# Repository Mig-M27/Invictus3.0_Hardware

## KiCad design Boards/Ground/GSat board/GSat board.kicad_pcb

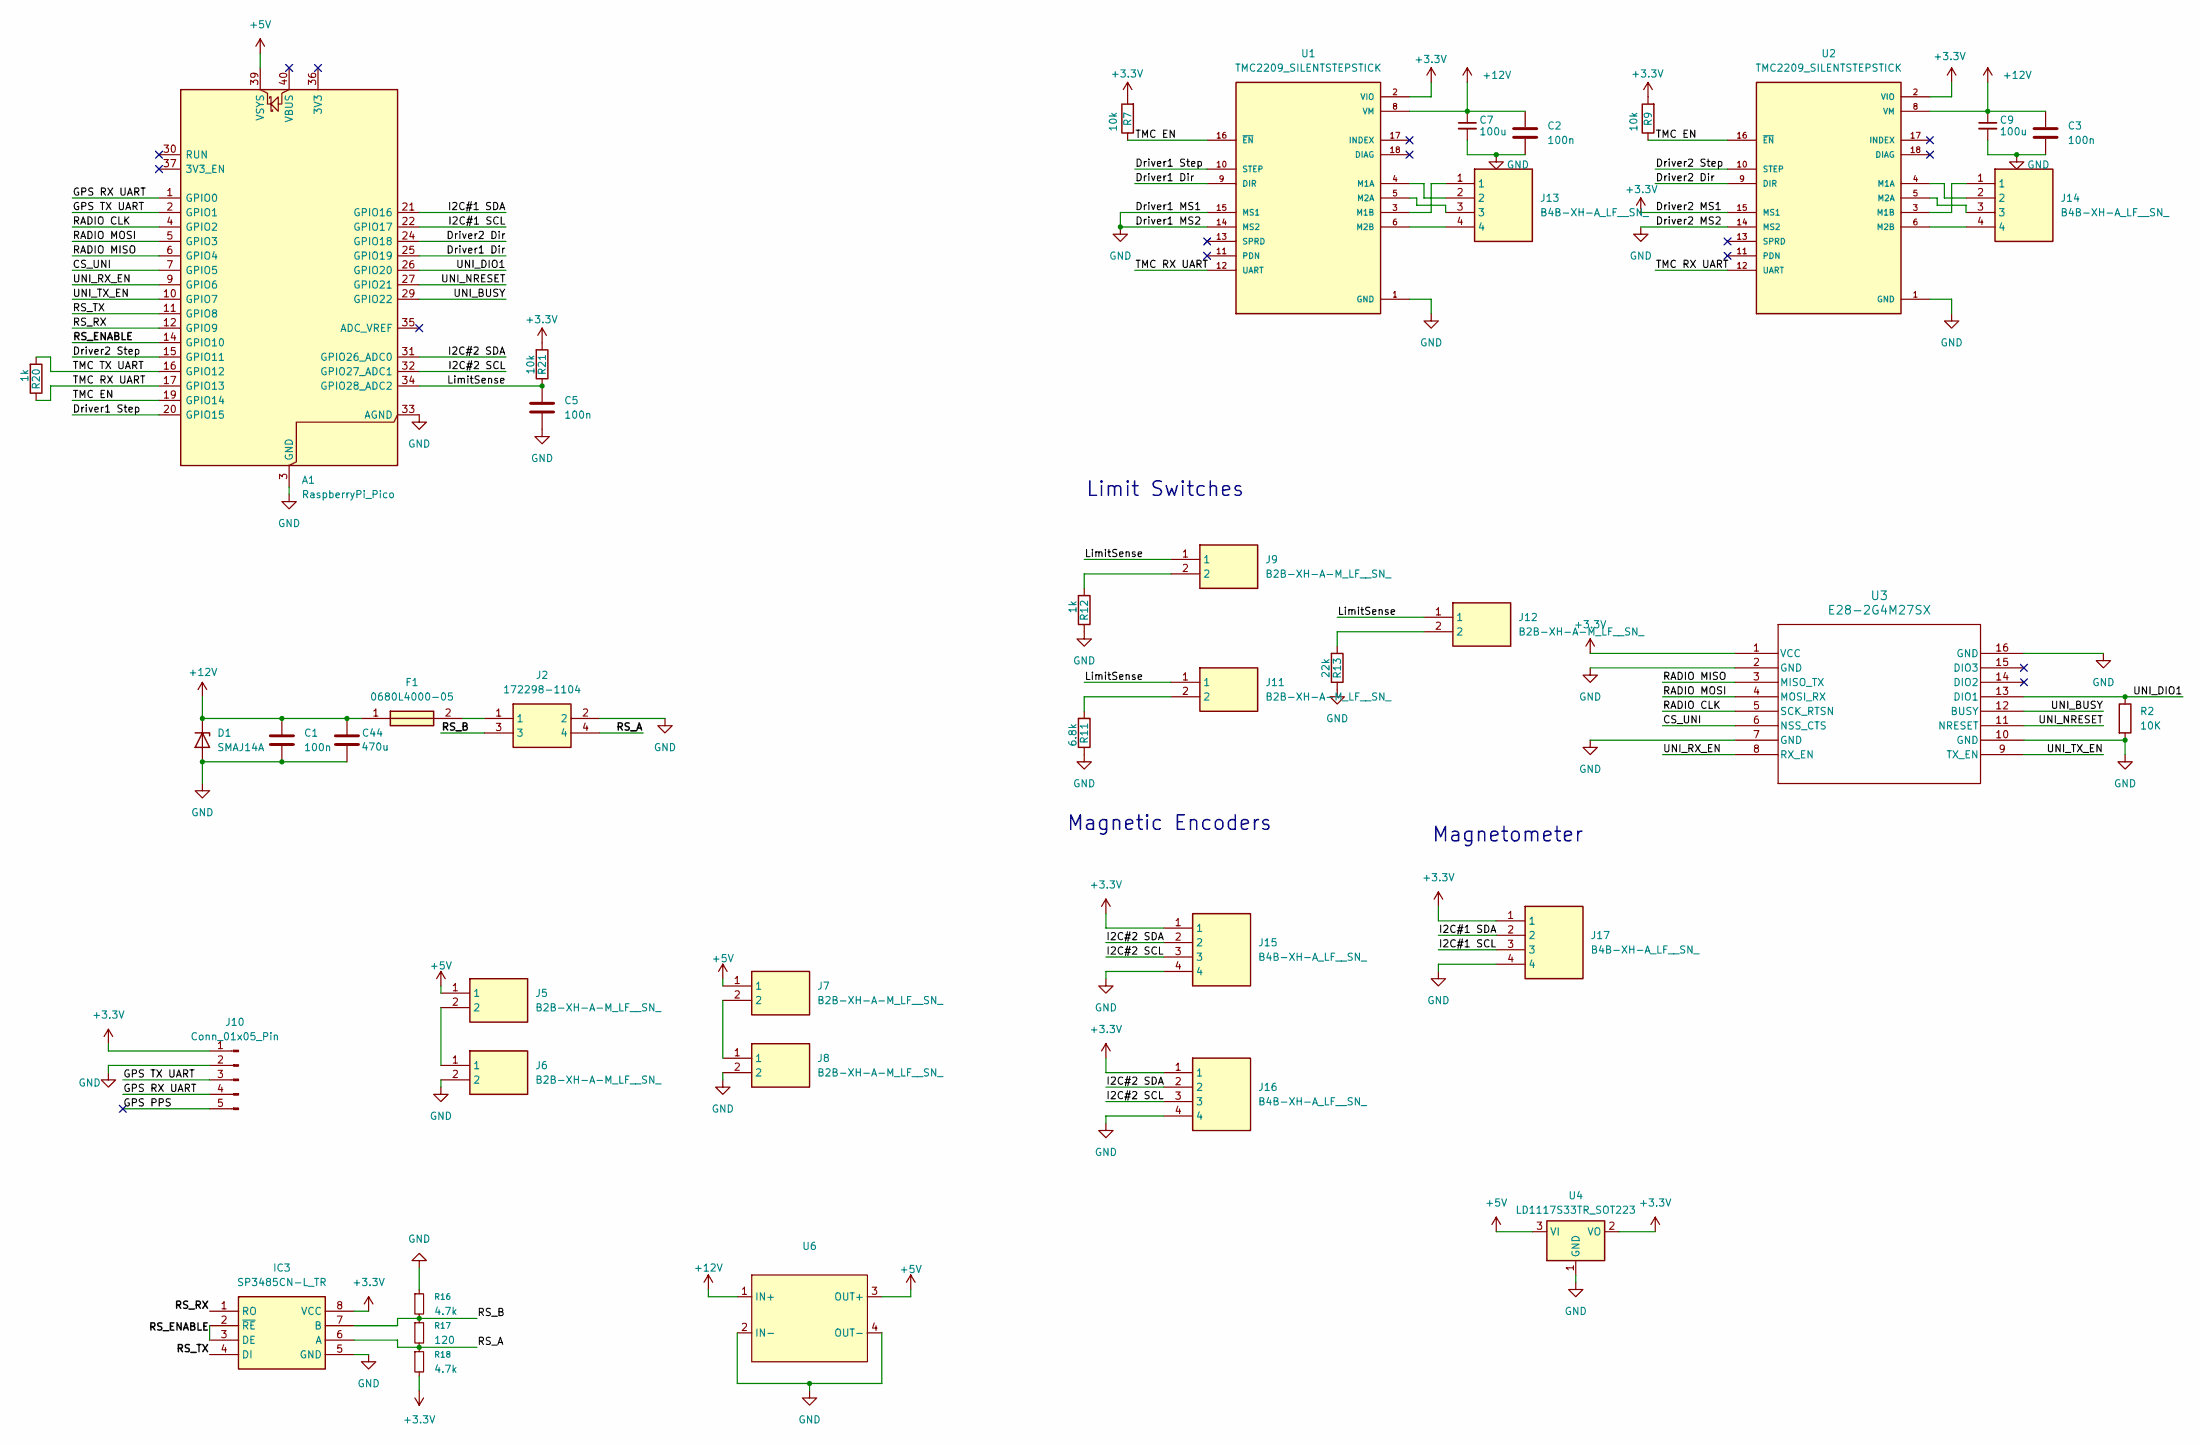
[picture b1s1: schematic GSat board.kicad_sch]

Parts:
A1: RaspberryPi_Pico; RaspberryPi_Pico_Common_Unspecified
C1, C2, C3, C5: 100n; C_0805_2012Metric_Pad1.18x1.45mm_HandSolder
C7, C9: 100u; CP_Elec_6.3x7.7
C44: 470u; CP_Elec_10x10
D1: SMAJ14A; D_SMB
F1: 0680L4000-05; Fuse_2512_6332Metric; Mouser Part Number 530-0ABB-6000-TM
IC3: SP3485CN-L_TR; SOIC127P600X175-8N; Mouser Part Number 701-SP3485CN-L/TR
J2: 172298-1104; 172298-YY04; Mouser Part Number 538-172298-1104
J5, J6, J7, J8, J9, J11, J12: B2B-XH-A-M_LF__SN_; B2BXHAMLFSN; Mouser Part Number 306-B2B-XH-A-MLFS
J10: Conn_01x05_Pin; PinSocket_1x05_P2.54mm_Vertical
J13, J14, J15, J16, J17: B4B-XH-A_LF__SN_; B4BXHALFSN; Mouser Part Number 306-B4BXHALFSN
R2: 10K; R_0805_2012Metric_Pad1.20x1.40mm_HandSolder
R7, R9, R21: 10k; R_0805_2012Metric_Pad1.20x1.40mm_HandSolder
R11: 6.8k; R_0805_2012Metric_Pad1.20x1.40mm_HandSolder
R12, R20: 1k; R_0805_2012Metric_Pad1.20x1.40mm_HandSolder
R13: 22k; R_0805_2012Metric_Pad1.20x1.40mm_HandSolder
R16: 4.7k; R_0603_1608Metric_Pad0.98x0.95mm_HandSolder
R17: 120; R_0603_1608Metric_Pad0.98x0.95mm_HandSolder
R18: 4.7k; R_0805_2012Metric_Pad1.20x1.40mm_HandSolder
U1, U2: TMC2209_SILENTSTEPSTICK; MODULE_TMC2209_SILENTSTEPSTICK; PARTREV 1.20
U3: E28-2G4M27SX; Radio_Module_PST
U4: LD1117S33TR_SOT223; SOT-223-3_TabPin2
U6: DCDC_Module

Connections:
+3.3V: IC3.8 (VCC), J10.1, J15.1, J16.1, J17.1, R7.2, R9.2, R18.2, R21.2, U1.2 (VIO), U2.2 (VIO), U2.15 (MS1), U3.1 (VCC), U4.2 (VO)
+5V: A1.39 (VSYS), J5.1, J7.1, U4.3 (VI), U6.3 (OUT+)
+12V: C1.1, C2.1, C3.1, C7.1, C9.1, C44.1, D1.1 (K), F1.1, U1.8 (VM), U2.8 (VM), U6.1 (IN+)
/CS_UNI: A1.7 (GPIO5), U3.6 (NSS_CTS)
/Driver1 Dir: A1.25 (GPIO19), U1.9 (DIR)
/Driver1 Step: A1.20 (GPIO15), U1.10 (STEP)
/Driver2 Dir: A1.24 (GPIO18), U2.9 (DIR)
/Driver2 Step: A1.15 (GPIO11), U2.10 (STEP)
/GPS PPS: J10.5
/GPS RX UART: A1.1 (GPIO0), J10.4
/GPS TX UART: A1.2 (GPIO1), J10.3
/I2C#1 SCL: A1.22 (GPIO17), J17.3
/I2C#1 SDA: A1.21 (GPIO16), J17.2
/I2C#2 SCL: A1.32 (GPIO27_ADC1), J15.3, J16.3
/I2C#2 SDA: A1.31 (GPIO26_ADC0), J15.2, J16.2
/LimitSense: A1.34 (GPIO28_ADC2), C5.1, J9.1, J11.1, J12.1, R21.1
/RADIO CLK: A1.4 (GPIO2), U3.5 (SCK_RTSN)
/RADIO MISO: A1.6 (GPIO4), U3.3 (MISO_TX)
/RADIO MOSI: A1.5 (GPIO3), U3.4 (MOSI_RX)
/RS_A: IC3.6 (A), J2.4, R17.2, R18.1
/RS_B: IC3.7 (B), J2.3, R16.2, R17.1
/RS_ENABLE: A1.14 (GPIO10), IC3.2 (~RE), IC3.3 (DE)
/RS_RX: A1.12 (GPIO9), IC3.1 (RO)
/RS_TX: A1.11 (GPIO8), IC3.4 (DI)
/TMC EN: A1.19 (GPIO14), R7.1, R9.1, U1.16 (~EN), U2.16 (~EN)
/TMC RX UART: A1.17 (GPIO13), R20.1, U1.12 (UART), U2.12 (UART)
/TMC TX UART: A1.16 (GPIO12), R20.2
/UNI_BUSY: A1.29 (GPIO22), U3.12 (BUSY)
/UNI_DIO1: A1.26 (GPIO20), R2.1, U3.13 (DIO1)
/UNI_NRESET: A1.27 (GPIO21), U3.11 (NRESET)
/UNI_RX_EN: A1.9 (GPIO6), U3.8 (RX_EN)
/UNI_TX_EN: A1.10 (GPIO7), U3.9 (TX_EN)
GND: A1.3 (GND), A1.8 (GND), A1.13 (GND), A1.18 (GND), A1.23 (GND), A1.28 (GND), A1.33 (AGND), A1.38 (GND), C1.2, C2.2, C3.2, C5.2, C7.2, C9.2, C44.2, D1.2 (A), IC3.5 (GND), J2.2, J6.2, J8.2, J10.2, J15.4, J16.4, J17.4, R2.2, R11.1, R12.1, R13.1, R16.1, U1.1 (GND), U1.7 (GND), U1.14 (MS2), U1.15 (MS1), U2.1 (GND), U2.7 (GND), U2.14 (MS2), U3.2 (GND), U3.7 (GND), U3.10 (GND), U3.16 (GND), U4.1 (GND), U6.2 (IN-), U6.4 (OUT-)
unnamed: F1.2, J2.1
unnamed: J5.2, J6.1
unnamed: J7.2, J8.1
unnamed: J9.2, R12.2
unnamed: J11.2, R11.2
unnamed: J12.2, R13.2
unnamed: J13.2, U1.4 (M1A)
unnamed: J13.1, U1.3 (M1B)
unnamed: J13.3, U1.5 (M2A)
unnamed: J13.4, U1.6 (M2B)
unnamed: J14.2, U2.4 (M1A)
unnamed: J14.1, U2.3 (M1B)
unnamed: J14.3, U2.5 (M2A)
unnamed: J14.4, U2.6 (M2B)

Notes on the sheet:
Magnetic Encoders
Limit Switches
Magnetometer

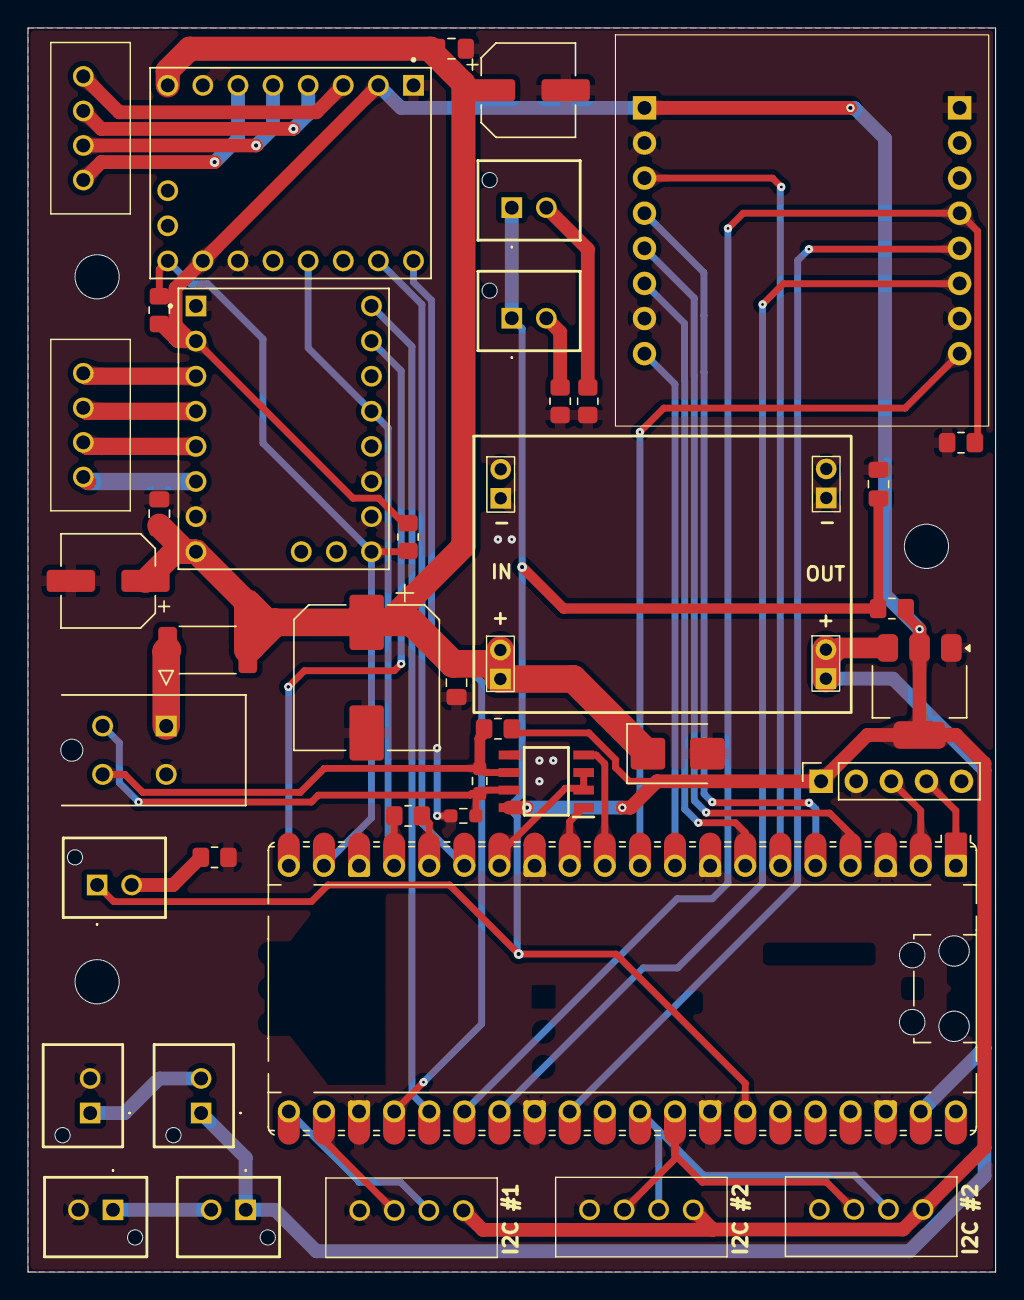
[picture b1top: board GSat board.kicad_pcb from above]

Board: 2 copper layers, 70.0 x 90.0 mm, 41 parts (0 on the bottom side), 46 nets.

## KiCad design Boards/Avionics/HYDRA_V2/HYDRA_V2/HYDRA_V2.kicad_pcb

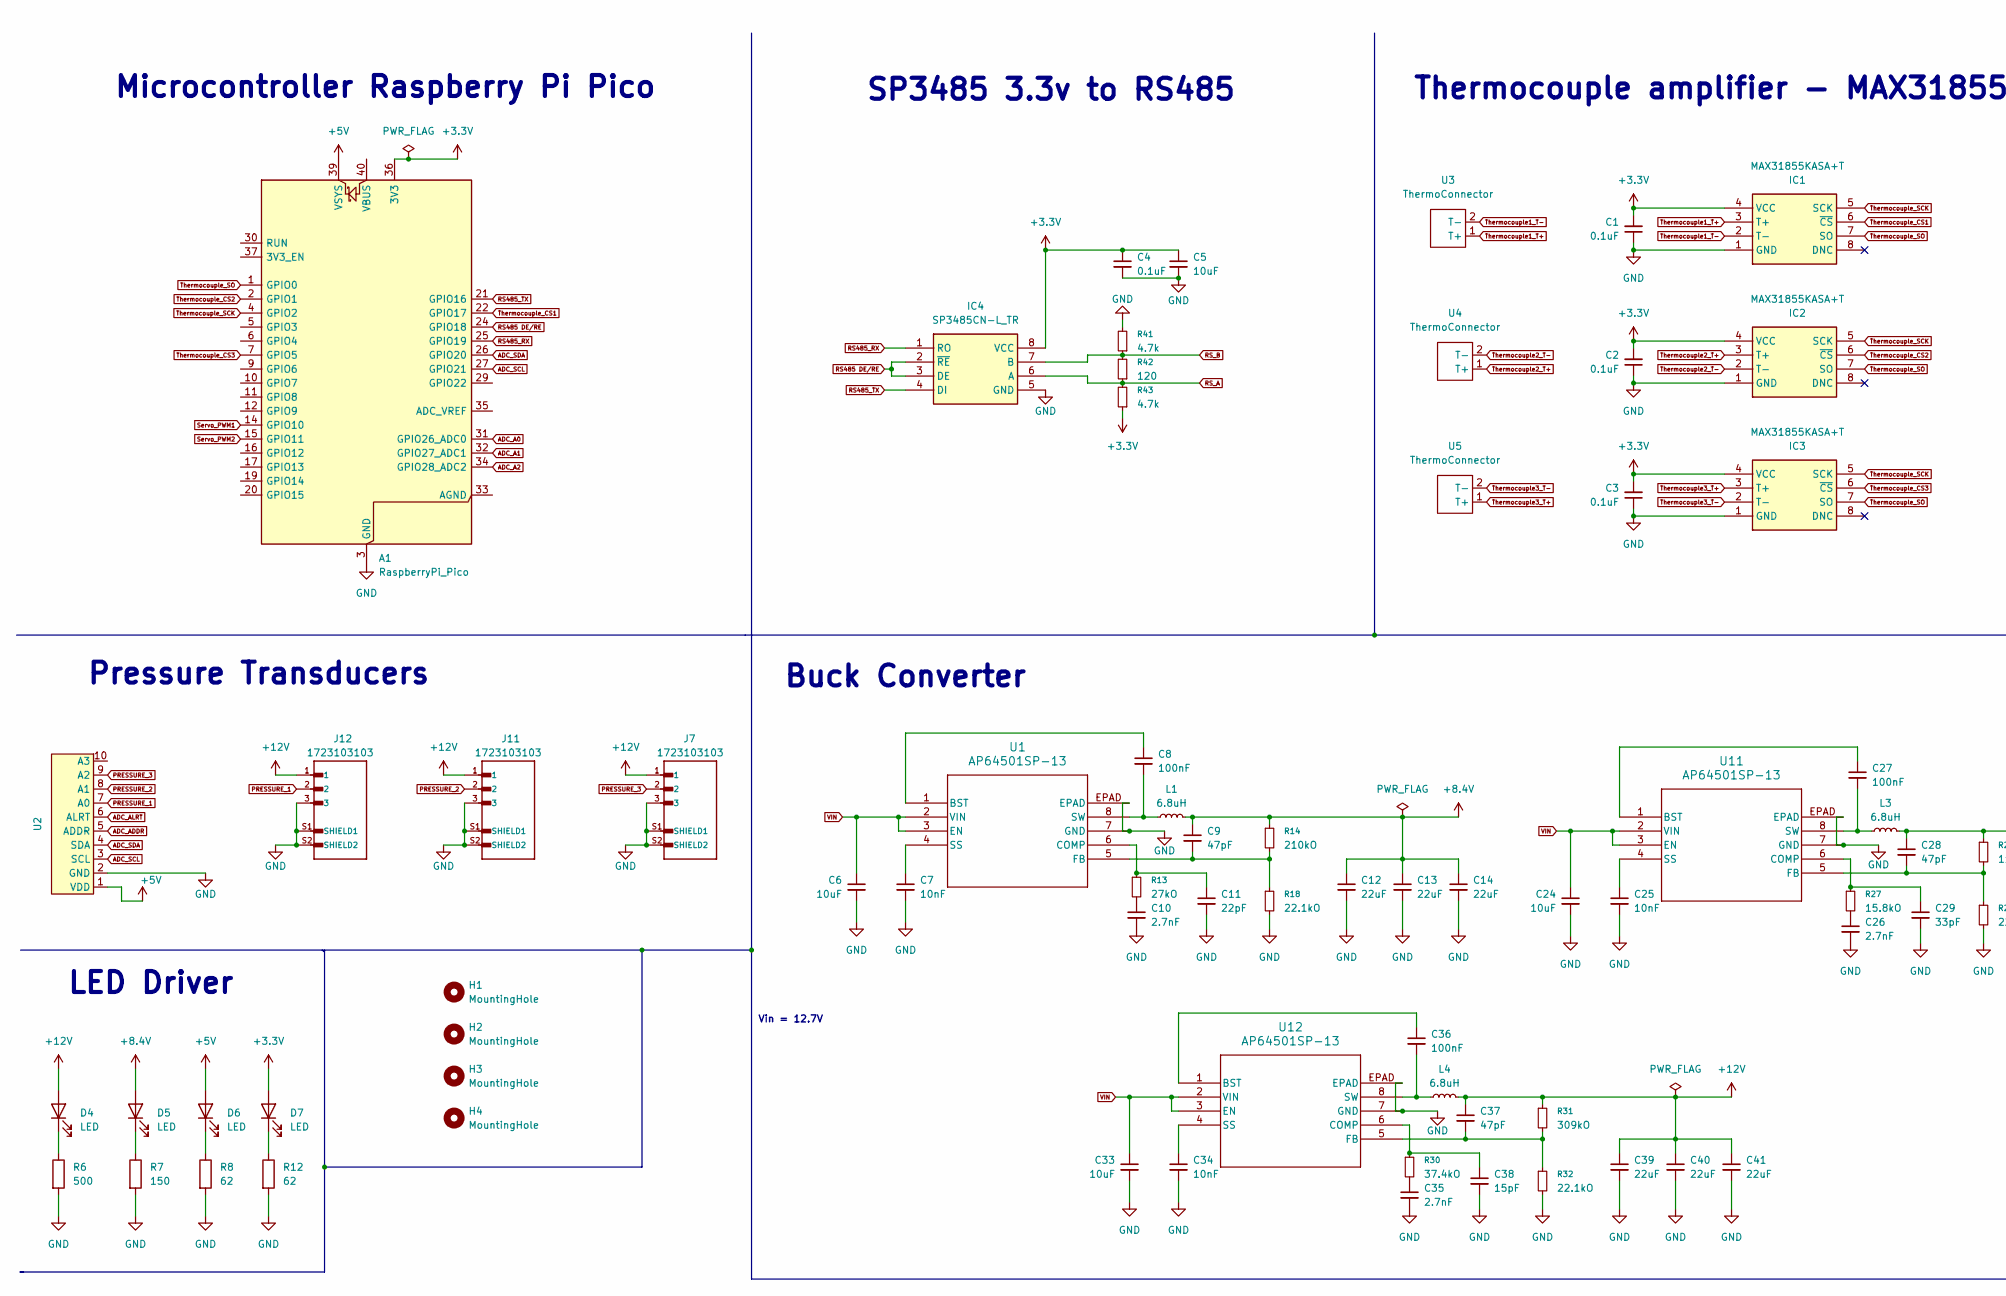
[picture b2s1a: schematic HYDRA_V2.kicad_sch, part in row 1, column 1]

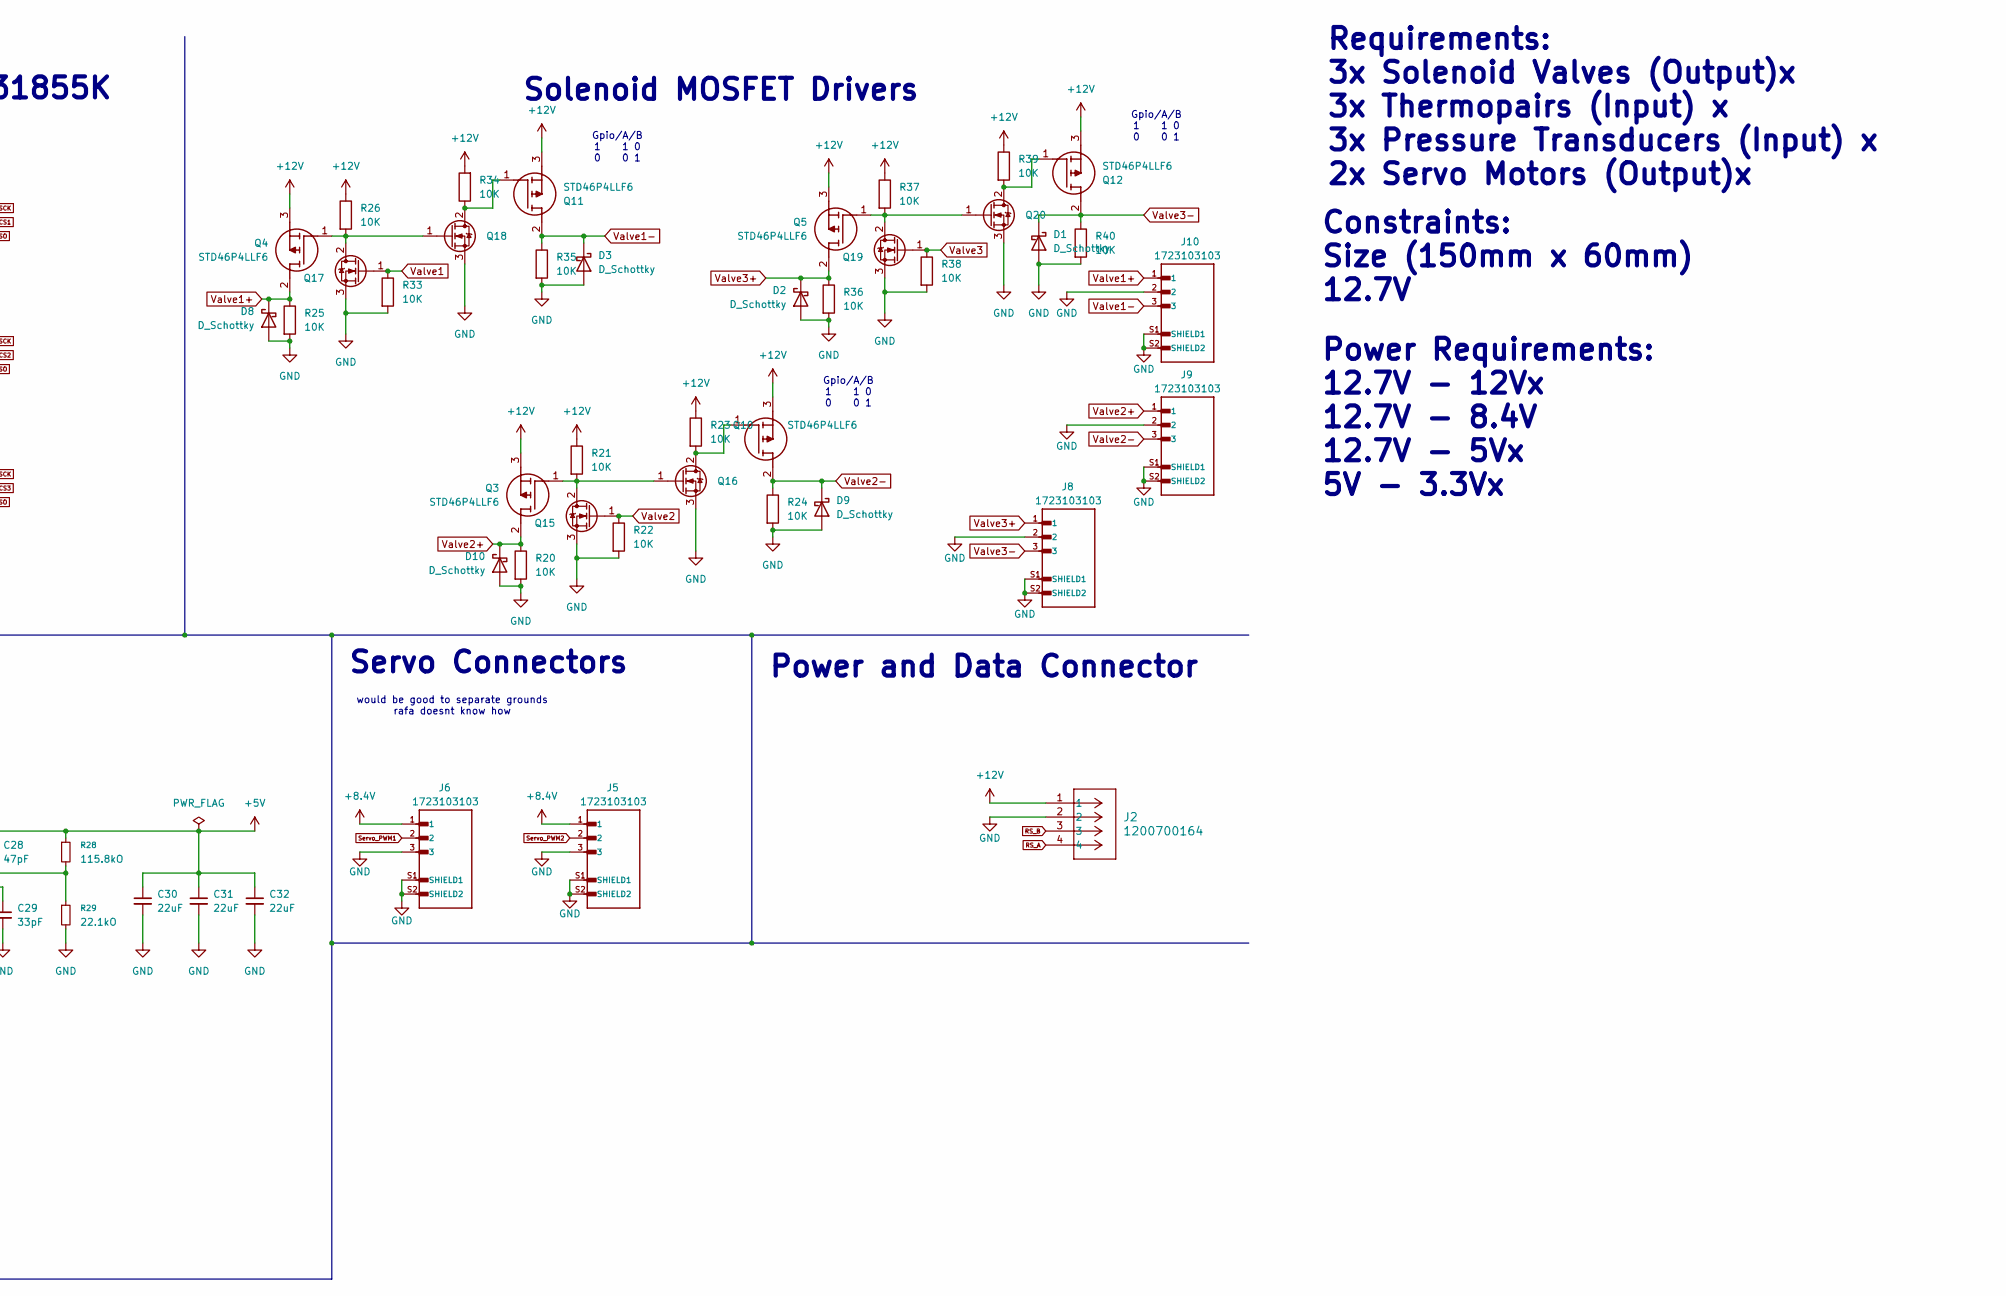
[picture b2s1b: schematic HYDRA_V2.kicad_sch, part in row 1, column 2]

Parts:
A1: RaspberryPi_Pico; RaspberryPi_Pico_Common_Unspecified
C1, C2, C3, C4: 0.1uF; C_0805_2012Metric
C5: 10uF; C_0805_2012Metric
C6, C24, C33: 10uF; C_0805_2012Metric_Pad1.18x1.45mm_HandSolder
C7, C25, C34: 10nF; C_0603_1608Metric_Pad1.08x0.95mm_HandSolder
C8, C27, C36: 100nF; C_0603_1608Metric_Pad1.08x0.95mm_HandSolder
C9, C28, C37: 47pF; C_0603_1608Metric_Pad1.08x0.95mm_HandSolder
C10, C26, C35: 2.7nF; C_0603_1608Metric_Pad1.08x0.95mm_HandSolder
C11: 22pF; C_0603_1608Metric_Pad1.08x0.95mm_HandSolder
C12, C13, C14, C30, C31, C32, C39, C40, C41: 22uF; C_0603_1608Metric_Pad1.08x0.95mm_HandSolder
C29: 33pF; C_0603_1608Metric_Pad1.08x0.95mm_HandSolder
C38: 15pF; C_0603_1608Metric_Pad1.08x0.95mm_HandSolder
D1, D2, D3, D8, D9, D10: D_Schottky
D4, D5, D6, D7: LED; LEDC1608X100N
H1, H2, H3, H4: MountingHole; MountingHole_3.2mm_M3_ISO7380
IC1, IC2, IC3: MAX31855KASA+T; SOIC127P600X175-8N; Mouser Part Number 700-MAX31855KASA+T
IC4: SP3485CN-L_TR; SOIC127P600X175-8N; Mouser Part Number 701-SP3485CN-L/TR
J2: 1200700164; CONN_1200700164_MOL
J5, J6, J7, J8, J9, J10, J11, J12: 1723103103; MOLEX_1723103103; PARTREV B1; DigiKey_Part_Number 900-1723103103-ND
L1, L3, L4: 6.8uH; SPM10054T6R8MHZR
Q3, Q4, Q5, Q10, Q11, Q12: STD46P4LLF6; Mouser Part Number 511-STD46P4LLF6
Q15, Q16, Q17, Q18, Q19, Q20: IRLB3813PBF-ND; SOT-223
R6: 500; R_0805_2012Metric
R7: 150; R_0805_2012Metric
R8, R12: 62; R_0805_2012Metric
R13: 27kO; R_0603_1608Metric_Pad0.98x0.95mm_HandSolder
R14: 210kO; R_0603_1608Metric_Pad0.98x0.95mm_HandSolder
R18, R29, R32: 22.1kO; R_0603_1608Metric_Pad0.98x0.95mm_HandSolder
R20, R21, R22, R23, R24, R25, R26, R33, R34, R35, R36, R37, R38, R39, R40: 10K; R_0805_2012Metric_Pad1.20x1.40mm_HandSolder
R27: 15.8kO; R_0603_1608Metric_Pad0.98x0.95mm_HandSolder
R28: 115.8kO; R_0603_1608Metric_Pad0.98x0.95mm_HandSolder
R30: 37.4kO; R_0603_1608Metric_Pad0.98x0.95mm_HandSolder
R31: 309kO; R_0603_1608Metric_Pad0.98x0.95mm_HandSolder
R41, R43: 4.7k; R_0603_1608Metric_Pad0.98x0.95mm_HandSolder
R42: 120; R_0603_1608Metric_Pad0.98x0.95mm_HandSolder
U1, U11, U12: AP64501SP-13; SOP_AP64501SP-13_DIO
U2: Pressure_Amp
U3, U4, U5: ThermoConnector; Thermo Type K PCB Connector

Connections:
+3.3V: A1.36 (3V3), C1.2, C2.2, C3.2, C4.1, C5.1, D7.2 (A), IC1.4 (VCC), IC2.4 (VCC), IC3.4 (VCC), IC4.8 (VCC), R43.1
+5V: A1.39 (VSYS), C28.1, C30.1, C31.1, C32.1, D6.2 (A), L3.2, R28.1, U2.1 (VDD)
+8.4V: C9.1, C12.1, C13.1, C14.1, D5.2 (A), J5.1, J6.1, L1.2, R14.1
+12V: C37.1, C39.1, C40.1, C41.1, D4.2 (A), J2.1, J7.1, J11.1, J12.1, L4.2, Q3.3 (S), Q4.3 (S), Q5.3 (S), Q10.3 (S), Q11.3 (S), Q12.3 (S), R21.1, R23.1, R26.1, R31.1, R34.2, R37.1, R39.1; also elsewhere on the board
ADC_A0: A1.31 (GPIO26_ADC0)
ADC_A1: A1.32 (GPIO27_ADC1)
ADC_A2: A1.34 (GPIO28_ADC2)
ADC_ADDR: U2.5 (ADDR)
ADC_ALRT: U2.6 (ALRT)
ADC_SCL: A1.27 (GPIO21), U2.3 (SCL)
ADC_SDA: A1.26 (GPIO20), U2.4 (SDA)
GND: A1.3 (GND), A1.8 (GND), A1.13 (GND), A1.18 (GND), A1.23 (GND), A1.28 (GND), A1.38 (GND), C1.1, C2.1, C3.1, C4.2, C5.2, C6.2, C7.2, C10.2, C11.2, C12.2, C13.2, C14.2, C24.2, C25.2, C26.2, C29.2, C30.2, C31.2, C32.2, C33.2, C34.2, C35.2, C38.2, C39.2, C40.2, C41.2, D1.2 (A), D2.2 (A), D3.2 (A), D8.2 (A), D9.2 (A), D10.2 (A), IC1.1 (GND), IC2.1 (GND), IC3.1 (GND), IC4.5 (GND), J2.2, J5.3, J5.S1 (SHIELD1), J5.S2 (SHIELD2), J6.3, J6.S1 (SHIELD1), J6.S2 (SHIELD2), J7.3, J7.S1 (SHIELD1), J7.S2 (SHIELD2), J8.2, J8.S1 (SHIELD1), J8.S2 (SHIELD2), J9.2, J9.S1 (SHIELD1), J9.S2 (SHIELD2), J10.2, J10.S1 (SHIELD1), J10.S2 (SHIELD2), J11.3, J11.S1 (SHIELD1), J11.S2 (SHIELD2), J12.3, J12.S1 (SHIELD1), J12.S2 (SHIELD2), Q15.3 (S), Q16.3 (S), Q17.3 (S), Q18.3 (S), Q19.3 (S), Q20.3 (S), R6.2, R7.2, R8.2, R12.2, R18.2, R20.2, R22.2, R24.2, R25.2, R29.2, R32.2, R33.2, R35.2, R36.2, R38.2, R40.2, R41.2, U1.7 (GND), U1.EPAD, U2.2 (GND), U11.7 (GND), U11.EPAD, U12.7 (GND), U12.EPAD; also elsewhere on the board
unnamed: C10.1, R13.2
unnamed: C26.1, R27.2
unnamed: C35.1, R30.2
unnamed: D4.1 (K), R6.1
unnamed: D5.1 (K), R7.1
unnamed: D6.1 (K), R8.1
unnamed: D7.1 (K), R12.1
unnamed: Q10.1 (G), Q16.2 (D), R23.2
unnamed: Q11.1 (G), Q18.2 (D), R34.1
unnamed: Q12.1 (G), Q20.2 (D), R39.2
unnamed: Q3.1 (G), Q15.2 (D), Q16.1 (G), R21.2
unnamed: Q4.1 (G), Q17.2 (D), Q18.1 (G), R26.2
unnamed: Q5.1 (G), Q19.2 (D), Q20.1 (G), R37.2
unnamed: C8.1, U1.1 (BST)
unnamed: C11.1, R13.1, U1.6 (COMP)
unnamed: C9.2, R14.2, R18.1, U1.5 (FB)
unnamed: C7.1, U1.4 (SS)
unnamed: C8.2, L1.1, U1.8 (SW)
unnamed: C27.1, U11.1 (BST)
unnamed: C29.1, R27.1, U11.6 (COMP)
unnamed: C28.2, R28.2, R29.1, U11.5 (FB)
unnamed: C25.1, U11.4 (SS)
unnamed: C27.2, L3.1, U11.8 (SW)
unnamed: C36.1, U12.1 (BST)
unnamed: C38.1, R30.1, U12.6 (COMP)
unnamed: C37.2, R31.2, R32.1, U12.5 (FB)
unnamed: C34.1, U12.4 (SS)
unnamed: C36.2, L4.1, U12.8 (SW)
PRESSURE_1: J12.2, U2.7 (A0)
PRESSURE_2: J11.2, U2.8 (A1)
PRESSURE_3: J7.2, U2.9 (A2)
RS485 DE/RE: A1.24 (GPIO18), IC4.2 (~RE), IC4.3 (DE)
RS485_RX: A1.25 (GPIO19), IC4.1 (RO)
RS485_TX: A1.21 (GPIO16), IC4.4 (DI)
RS_A: IC4.6 (A), J2.4, R42.1, R43.2; also elsewhere on the board
RS_B: IC4.7 (B), J2.3, R41.1, R42.2; also elsewhere on the board
Servo_PWM1: A1.14 (GPIO10), J6.2
Servo_PWM2: A1.15 (GPIO11), J5.2
Thermocouple1_T+: IC1.3 (T+), U3.1 (T+)
Thermocouple1_T-: IC1.2 (T-), U3.2 (T-)
Thermocouple2_T+: IC2.3 (T+), U4.1 (T+)
Thermocouple2_T-: IC2.2 (T-), U4.2 (T-)
Thermocouple3_T+: IC3.3 (T+), U5.1 (T+)
Thermocouple3_T-: IC3.2 (T-), U5.2 (T-)
Thermocouple_CS1: A1.22 (GPIO17), IC1.6 (~CS)
Thermocouple_CS2: A1.2 (GPIO1), IC2.6 (~CS)
Thermocouple_CS3: A1.7 (GPIO5), IC3.6 (~CS)
Thermocouple_SCK: A1.4 (GPIO2), IC1.5 (SCK), IC2.5 (SCK), IC3.5 (SCK)
Thermocouple_SO: A1.1 (GPIO0), IC1.7 (SO), IC2.7 (SO), IC3.7 (SO)
VIN: C6.1, C24.1, C33.1, U1.2 (VIN), U1.3 (EN), U11.2 (VIN), U11.3 (EN), U12.2 (VIN), U12.3 (EN)
Valve1: Q17.1 (G), R33.1
Valve1+: D8.1 (K), J10.1, Q4.2 (D), R25.1; also elsewhere on the board
Valve1-: D3.1 (K), J10.3, Q11.2 (D), R35.1; also elsewhere on the board
Valve2: Q15.1 (G), R22.1
Valve2+: D10.1 (K), J9.1, Q3.2 (D), R20.1; also elsewhere on the board
Valve2-: D9.1 (K), J9.3, Q10.2 (D), R24.1; also elsewhere on the board
Valve3: Q19.1 (G), R38.1
Valve3+: D2.1 (K), J8.1, Q5.2 (D), R36.1; also elsewhere on the board
Valve3-: D1.1 (K), J8.3, Q12.2 (D), R40.1; also elsewhere on the board

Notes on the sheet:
Pressure Transducers
Requirements: 3x Solenoid Valves (Output)x 3x Thermopairs (Input) x 3x Pressure Transducers (Input) x 2x Servo Motors (Output)x
Thermocouple amplifier - MAX31855K
Buck Converter
Power and Data Connector
Gpio/A/B 1 1 0 0 0 1
LED Driver
would be good to separate grounds rafa doesnt know how
Constraints: Size (150mm x 60mm) 12.7V
Vin = 12.7V
Microcontroller Raspberry Pi Pico
SP3485 3.3v to RS485
Solenoid MOSFET Drivers
Power Requirements: 12.7V - 12Vx 12.7V - 8.4V 12.7V - 5Vx 5V - 3.3Vx
Servo Connectors

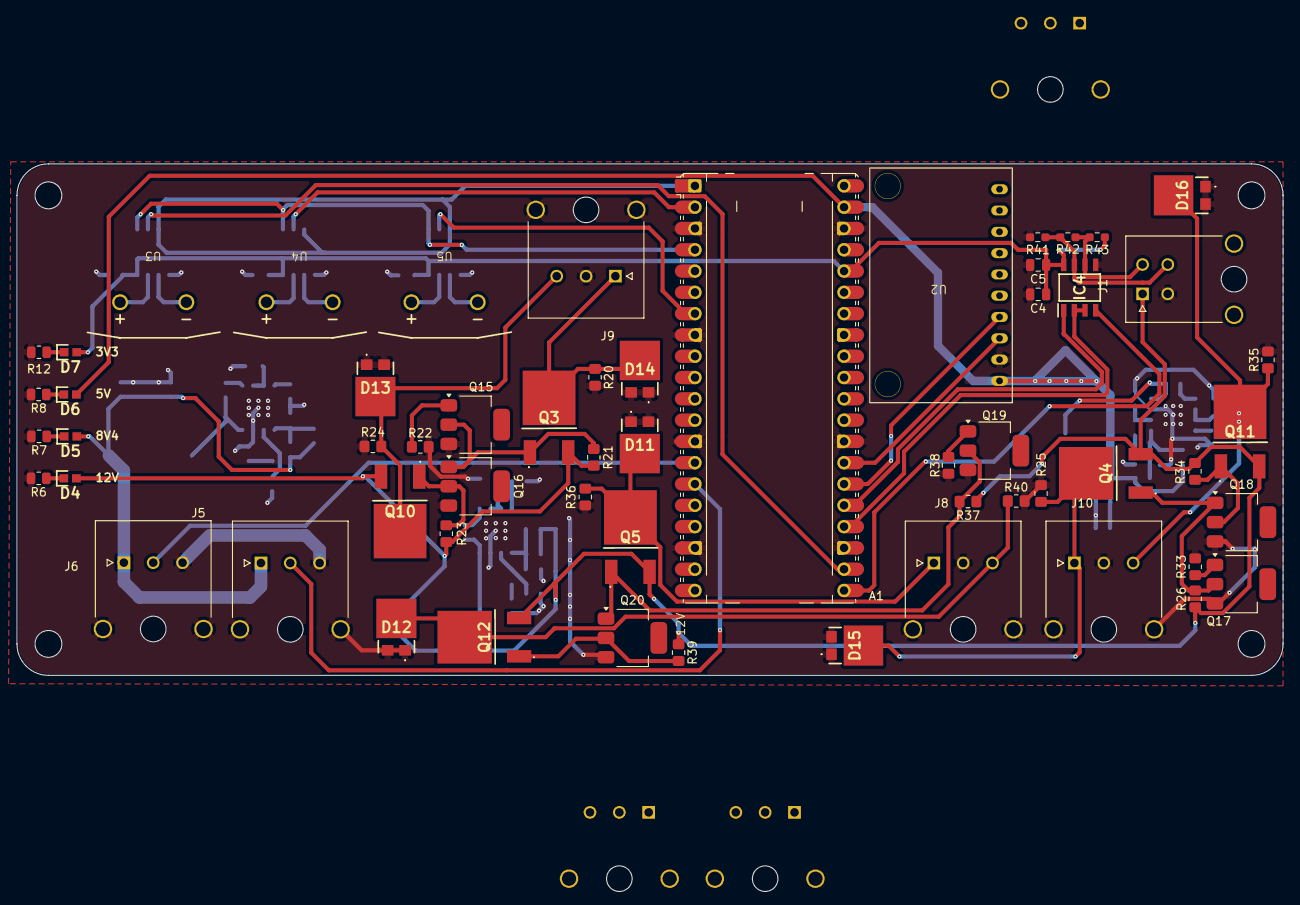
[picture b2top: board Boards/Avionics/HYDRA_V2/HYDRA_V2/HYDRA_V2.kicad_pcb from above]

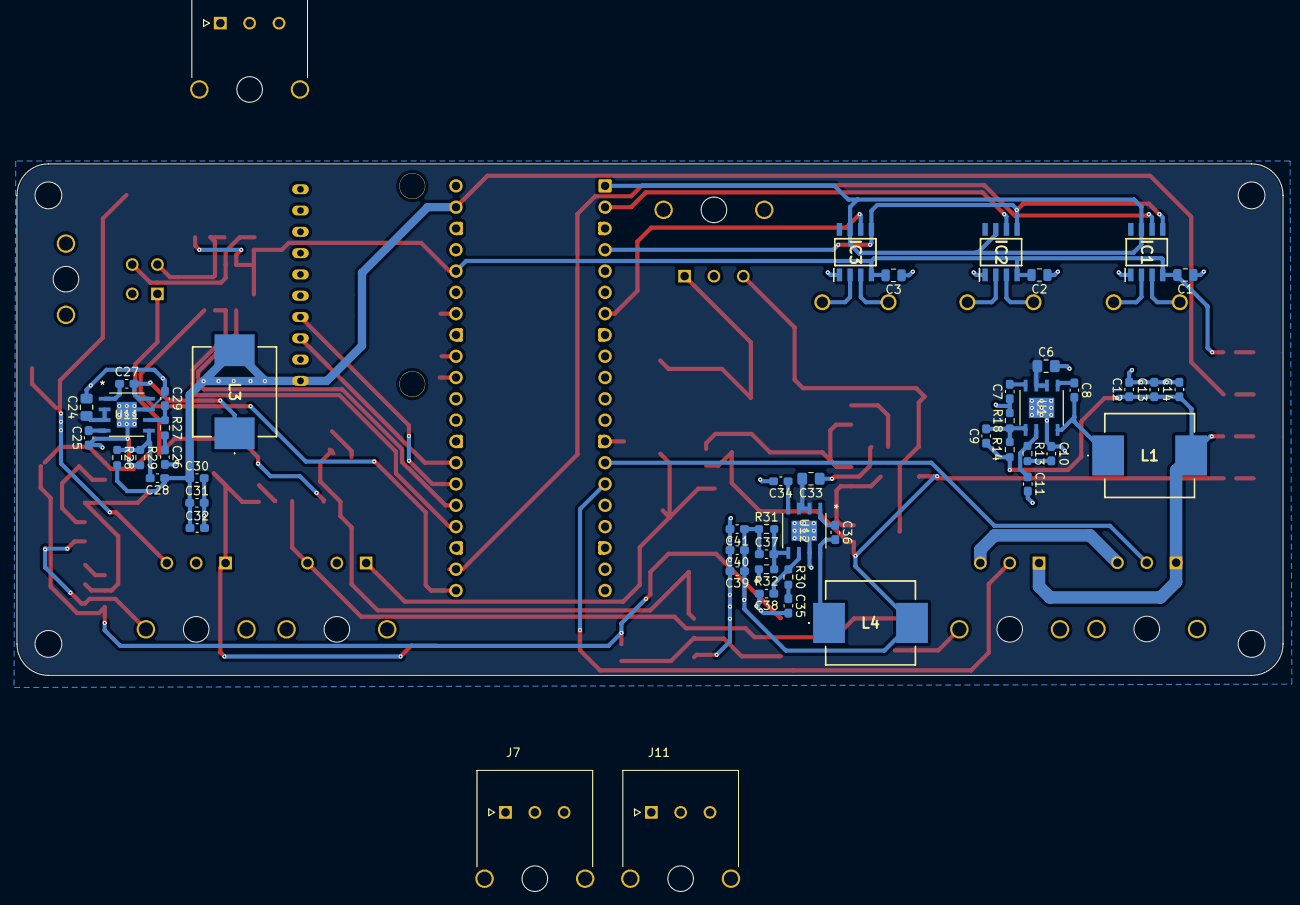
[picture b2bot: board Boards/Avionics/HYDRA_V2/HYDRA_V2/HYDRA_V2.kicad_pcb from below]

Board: 2 copper layers, 151.0 x 61.0 mm, 113 parts (51 on the bottom side), 66 nets.

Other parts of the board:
D11, D12, D13, D14, D15, D16: SS10PH102HM3_I; SS10PH102HM3I
J1: 1723163304; MOLEX_1723163304

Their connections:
+12V: J1.1; also elsewhere on the board
GND: D11.1 (A1), D11.2 (A2), D12.1 (A1), D12.2 (A2), D13.1 (A1), D13.2 (A2), D14.1 (A1), D14.2 (A2), D15.1 (A1), D15.2 (A2), D16.1 (A1), D16.2 (A2), J1.3; also elsewhere on the board
RS_A: J1.2; also elsewhere on the board
RS_B: J1.4; also elsewhere on the board
Valve1+: D15.3 (K); also elsewhere on the board
Valve1-: D16.3 (K); also elsewhere on the board
Valve2+: D14.3 (K); also elsewhere on the board
Valve2-: D13.3 (K); also elsewhere on the board
Valve3+: D11.3 (K); also elsewhere on the board
Valve3-: D12.3 (K); also elsewhere on the board

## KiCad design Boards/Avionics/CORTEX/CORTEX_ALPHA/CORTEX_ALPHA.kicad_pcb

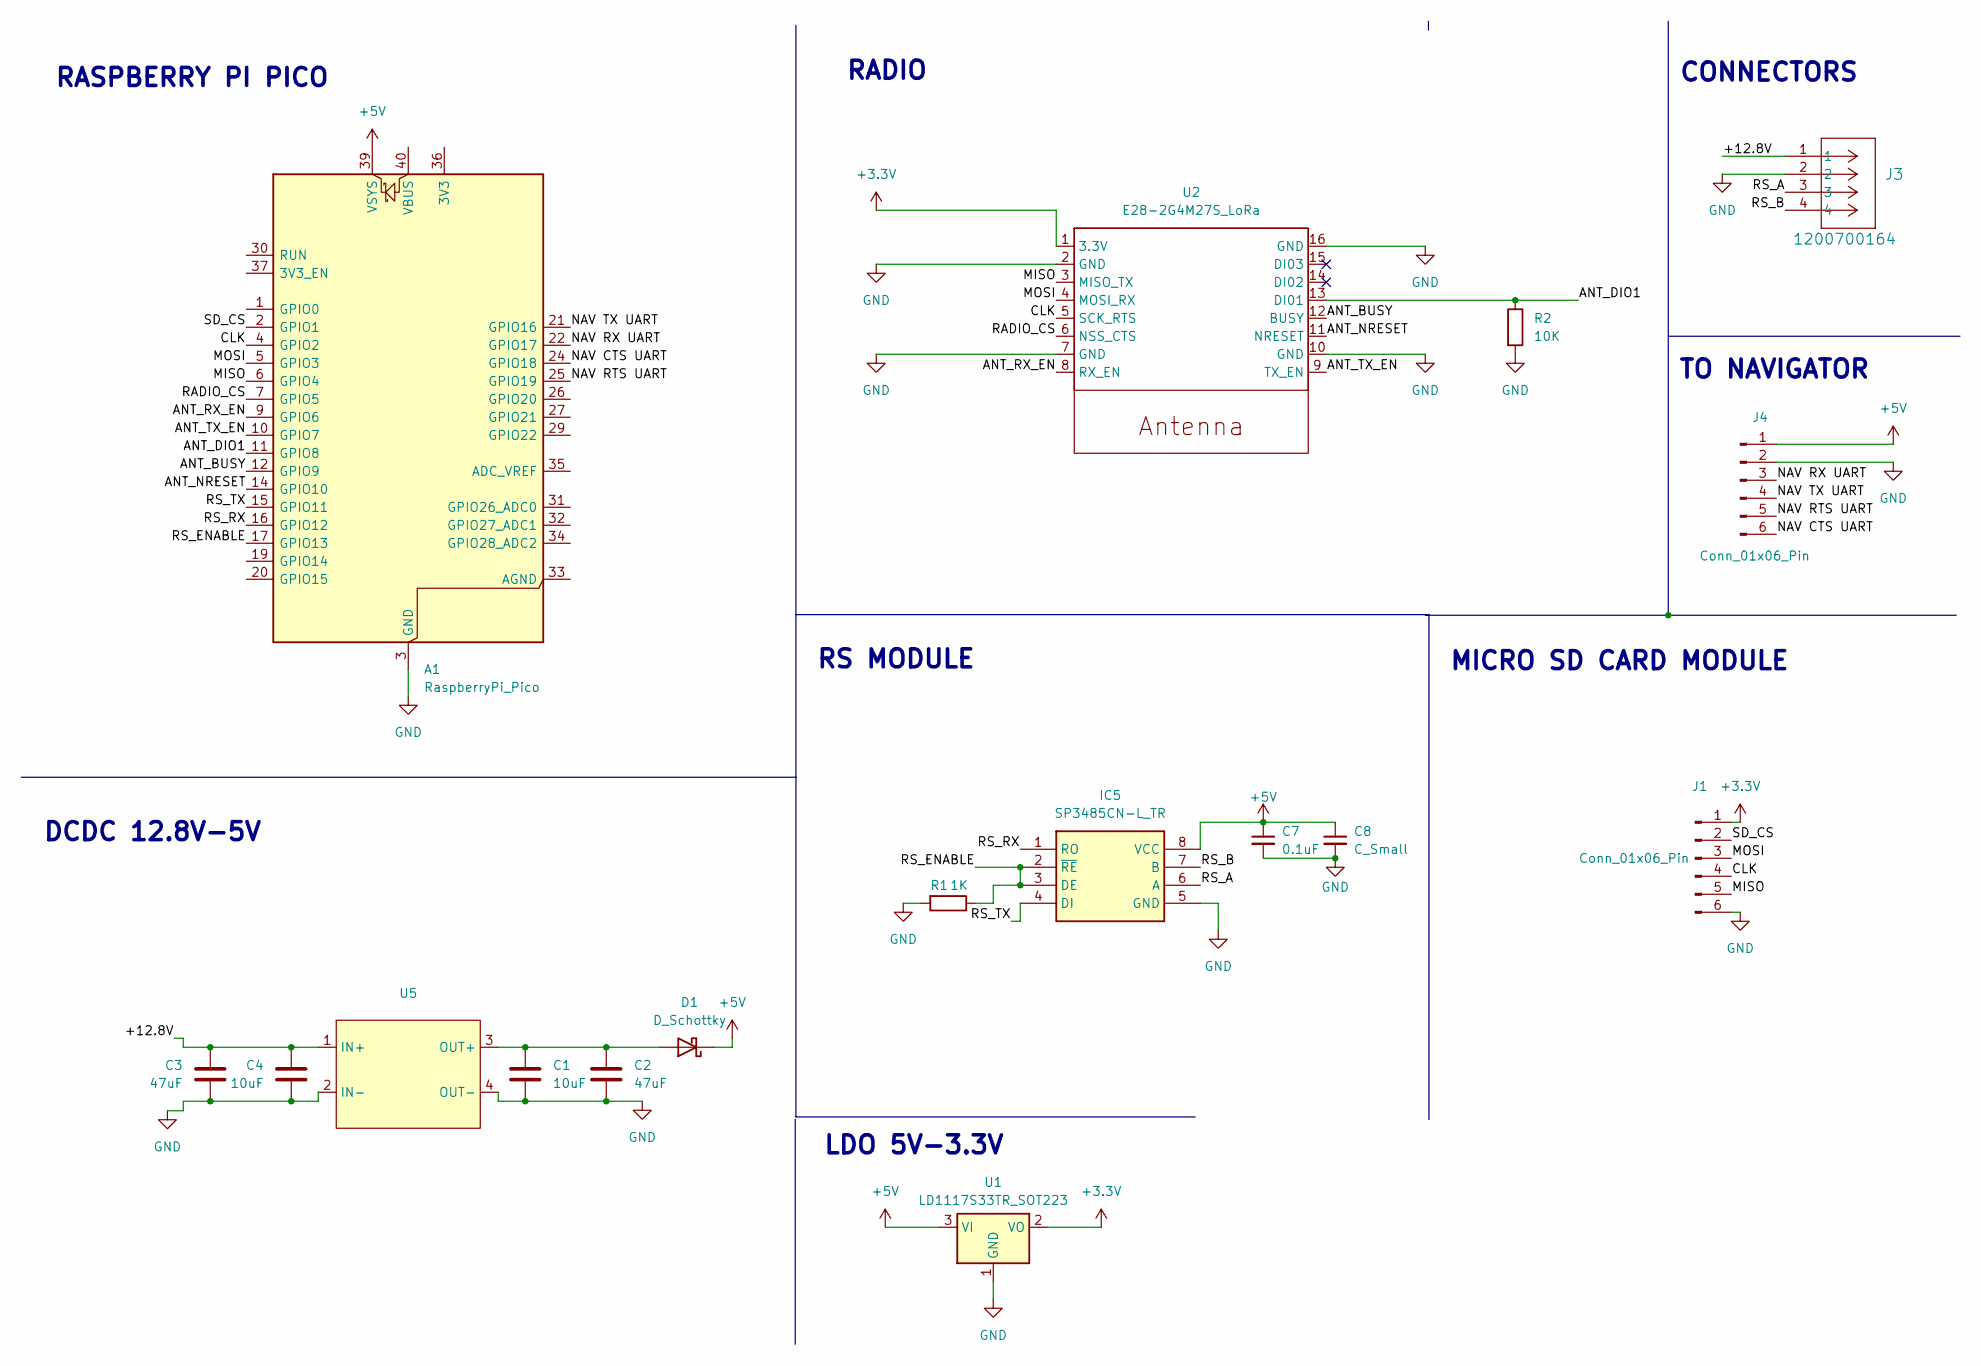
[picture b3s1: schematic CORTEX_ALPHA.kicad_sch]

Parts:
A1: RaspberryPi_Pico; RaspberryPi_Pico_Common_Unspecified
C1, C4: 10uF; C_0603_1608Metric_Pad1.08x0.95mm_HandSolder
C2, C3: 47uF; C_0603_1608Metric_Pad1.08x0.95mm_HandSolder
C7: 0.1uF; C_0805_2012Metric
C8: C_Small; C_0805_2012Metric
D1: D_Schottky; D_A-405_P7.62mm_Horizontal
IC5: SP3485CN-L_TR; SOIC-8_3.9x4.9mm_P1.27mm; Mouser Part Number 701-SP3485CN-L/TR
J1, J4: Conn_01x06_Pin; PinSocket_1x06_P2.54mm_Vertical
J3: 1200700164; CONN_1200700164_MOL
R1: 1K; R_0603_1608Metric_Pad0.98x0.95mm_HandSolder
R2: 10K; R_0603_1608Metric_Pad0.98x0.95mm_HandSolder
U1: LD1117S33TR_SOT223; SOT-223-3_TabPin2
U2: E28-2G4M27S_LoRa; Radio_Module_PST
U5: DCDC_Module

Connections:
+3.3V: J1.1, U1.2 (VO), U2.1 (3.3V)
+5V: A1.39 (VSYS), C7.1, C8.1, D1.1 (K), IC5.8 (VCC), J4.1, U1.3 (VI)
/+12.8V: C3.1, C4.1, J3.1, U5.1 (IN+)
/ANT_BUSY: A1.12 (GPIO9), U2.12 (BUSY)
/ANT_DIO1: A1.11 (GPIO8), R2.1, U2.13 (DI01)
/ANT_NRESET: A1.14 (GPIO10), U2.11 (NRESET)
/ANT_RX_EN: A1.9 (GPIO6), U2.8 (RX_EN)
/ANT_TX_EN: A1.10 (GPIO7), U2.9 (TX_EN)
/CLK: A1.4 (GPIO2), J1.4, U2.5 (SCK_RTS)
/MISO: A1.6 (GPIO4), J1.5, U2.3 (MISO_TX)
/MOSI: A1.5 (GPIO3), J1.3, U2.4 (MOSI_RX)
/NAV CTS UART: A1.24 (GPIO18), J4.6
/NAV RTS UART: A1.25 (GPIO19), J4.5
/NAV RX UART: A1.22 (GPIO17), J4.3
/NAV TX UART: A1.21 (GPIO16), J4.4
/RADIO_CS: A1.7 (GPIO5), U2.6 (NSS_CTS)
/RS_A: IC5.6 (A), J3.3
/RS_B: IC5.7 (B), J3.4
/RS_ENABLE: A1.17 (GPIO13), IC5.2 (~RE), IC5.3 (DE), R1.1
/RS_RX: A1.16 (GPIO12), IC5.1 (RO)
/RS_TX: A1.15 (GPIO11), IC5.4 (DI)
/SD_CS: A1.2 (GPIO1), J1.2
GND: A1.3 (GND), A1.8 (GND), A1.13 (GND), A1.18 (GND), A1.23 (GND), A1.28 (GND), A1.38 (GND), C1.2, C2.2, C3.2, C4.2, C7.2, C8.2, IC5.5 (GND), J1.6, J3.2, J4.2, R1.2, R2.2, U1.1 (GND), U2.2 (GND), U2.7 (GND), U2.10 (GND), U2.16 (GND), U5.2 (IN-), U5.4 (OUT-)
unnamed: C1.1, C2.1, D1.2 (A), U5.3 (OUT+)

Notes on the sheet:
LDO 5V-3.3V
TO NAVIGATOR
RASPBERRY PI PICO
RS MODULE
DCDC 12.8V-5V
CONNECTORS
MICRO SD CARD MODULE
RADIO
